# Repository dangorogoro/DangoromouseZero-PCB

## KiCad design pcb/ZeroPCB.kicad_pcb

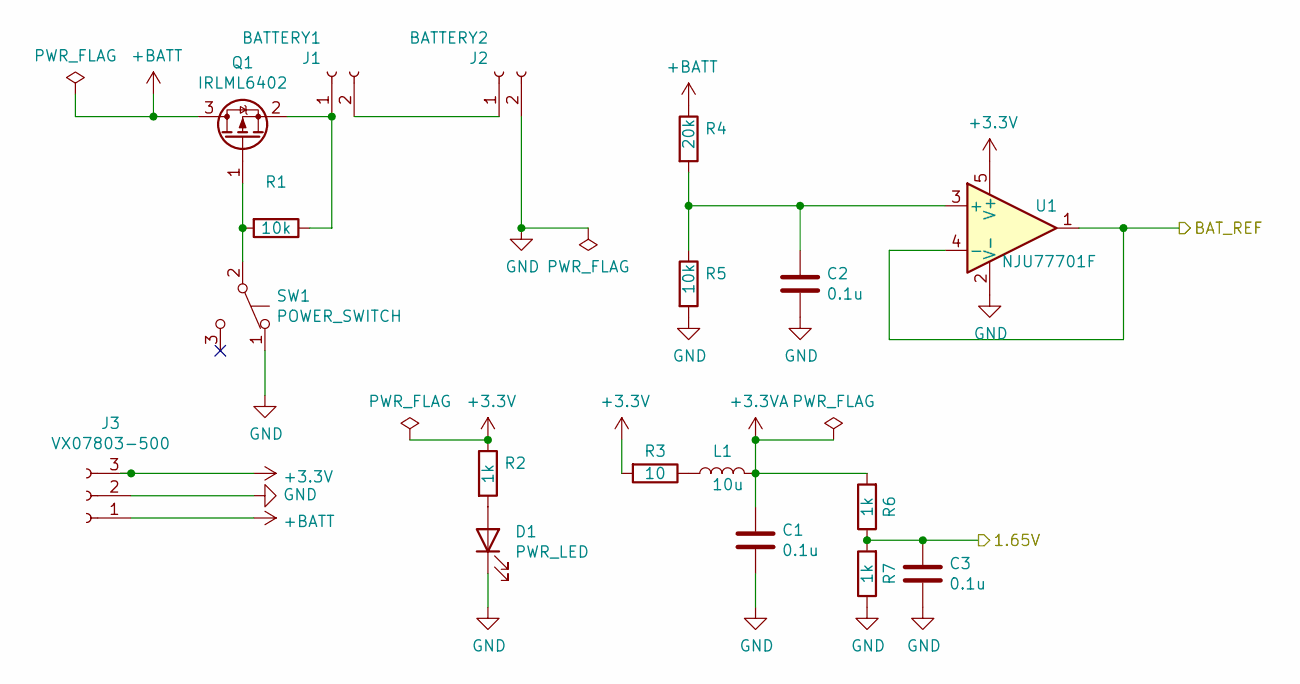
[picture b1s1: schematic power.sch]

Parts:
C1, C2, C3: 0.1u; C_0603_HandSoldering
D1: PWR_LED; LED_0603_HandSoldering
J1: BATTERY1; Molex_PicoBlade_53047-0210_02x1.25mm_Straight
J2: BATTERY2; Molex_PicoBlade_53047-0210_02x1.25mm_Straight
J3: VX07803-500; Pin_Header_Straight_1x03_Pitch2.54mm
L1: 10u; R_1210_HandSoldering
Q1: IRLML6402; SOT-23
R1, R5: 10k; R_0603_HandSoldering
R2, R6, R7: 1k; R_0603_HandSoldering
R3: 10; R_0603_HandSoldering
R4: 20k; R_0603_HandSoldering
SW1: POWER_SWITCH; Pin_Header_Straight_1x03_Pitch2.54mm
U1: NJU77701F; SOT-23-5_HandSoldering

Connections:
+3V3: J3.3, R2.1, R3.2, U1.5 (V+); also elsewhere on the board
+BATT: J3.1, Q1.3 (D), R4.1; also elsewhere on the board
/IRSensor/1.65V: C3.1, R6.1, R7.2; also elsewhere on the board
/MicroController/BAT_REF: U1.1, U1.4 (-); also elsewhere on the board
GND: C1.2, C2.2, C3.2, D1.1 (K), J2.2, J3.2, R5.2, R7.1, SW1.1 (A), U1.2 (V-); also elsewhere on the board
unnamed: C2.1, R4.2, R5.1, U1.3 (+)
unnamed: D1.2 (A), R2.2
unnamed 55: J1.1, Q1.2 (S), R1.1; also elsewhere on the board
unnamed: J1.2, J2.1
unnamed: L1.1, R3.1
unnamed: Q1.1 (G), R1.2, SW1.2 (B)

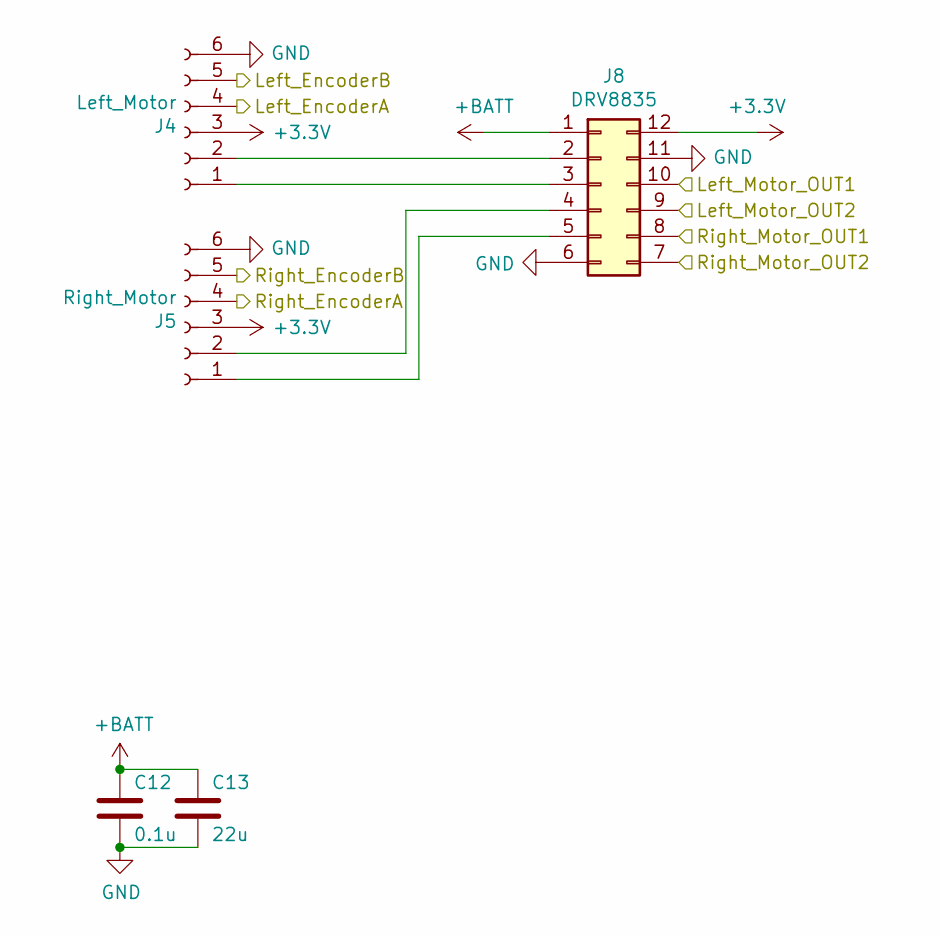
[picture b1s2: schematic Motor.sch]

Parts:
C12: 0.1u; C_0603_HandSoldering
C13: 22u; C_0603_HandSoldering
J4: Left_Motor; JST_XH_B6B-XH-AM_1x06_P2.50mm_Vertical
J5: Right_Motor; JST_XH_B6B-XH-AM_1x06_P2.50mm_Vertical
J8: DRV8835; DRV8835Board

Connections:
+3V3: J4.3, J5.3, J8.12; also elsewhere on the board
+BATT: C12.1, C13.1, J8.1; also elsewhere on the board
/MicroController/Left_EncoderA: J4.4; also elsewhere on the board
/MicroController/Left_EncoderB: J4.5; also elsewhere on the board
/MicroController/Left_Motor_OUT1: J8.10; also elsewhere on the board
/MicroController/Left_Motor_OUT2: J8.9; also elsewhere on the board
/MicroController/Right_EncoderA: J5.4; also elsewhere on the board
/MicroController/Right_EncoderB: J5.5; also elsewhere on the board
/MicroController/Right_Motor_OUT1: J8.8; also elsewhere on the board
/MicroController/Right_Motor_OUT2: J8.7; also elsewhere on the board
GND: C12.2, C13.2, J4.6, J5.6, J8.6, J8.11; also elsewhere on the board
unnamed: J4.1, J8.3
unnamed: J4.2, J8.2
unnamed: J5.1, J8.5
unnamed: J5.2, J8.4

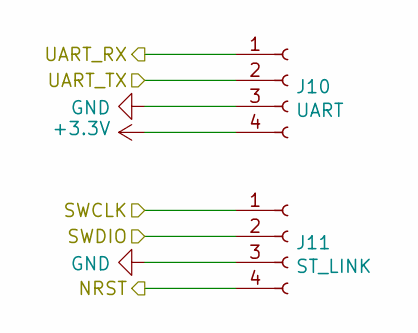
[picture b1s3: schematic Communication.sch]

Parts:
J10: UART; JST_SH_BM04B-SRSS-TB_1x04-1MP_P1.00mm_Vertical
J11: ST_LINK; JST_SH_BM04B-SRSS-TB_1x04-1MP_P1.00mm_Vertical

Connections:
+3V3: J10.4; also elsewhere on the board
/Communication/NRST: J11.4; also elsewhere on the board
/Communication/SWCLK: J11.1; also elsewhere on the board
/Communication/SWDIO: J11.2; also elsewhere on the board
/Communication/UART_RX: J10.1; also elsewhere on the board
/Communication/UART_TX: J10.2; also elsewhere on the board
GND: J10.3, J11.3; also elsewhere on the board

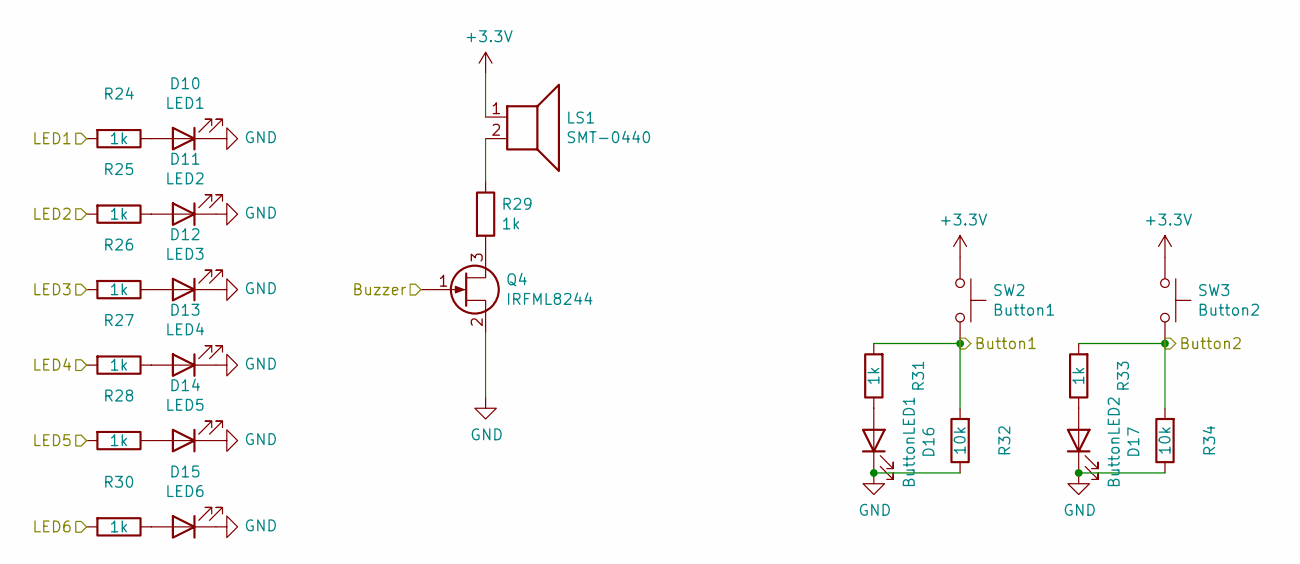
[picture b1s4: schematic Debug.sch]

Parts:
D10: LED1; LED_0603_HandSoldering
D11: LED2; LED_0603_HandSoldering
D12: LED3; LED_0603_HandSoldering
D13: LED4; LED_0603_HandSoldering
D14: LED5; LED_0603_HandSoldering
D15: LED6; LED_0603_HandSoldering
D16: ButtonLED1; LED_0603_HandSoldering
D17: ButtonLED2; LED_0603_HandSoldering
LS1: SMT-0440; SMT-0440-S-R
Q4: IRFML8244; SOT-23
R24, R25, R26, R27, R28, R29, R30, R31, R33: 1k; R_0603_HandSoldering
R32, R34: 10k; R_0603_HandSoldering
SW2: Button1; SW_SPST_EVQP2
SW3: Button2; SW_SPST_EVQP2

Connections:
+3V3: LS1.1, SW2.1, SW3.1; also elsewhere on the board
/Debug/Button1: R31.2, R32.2, SW2.2; also elsewhere on the board
/Debug/Button2: R33.2, R34.2, SW3.2; also elsewhere on the board
/Debug/Buzzer: Q4.1 (G); also elsewhere on the board
/Debug/LED1: R24.2; also elsewhere on the board
/Debug/LED2: R25.2; also elsewhere on the board
/Debug/LED3: R26.2; also elsewhere on the board
/Debug/LED4: R27.2; also elsewhere on the board
/Debug/LED5: R28.2; also elsewhere on the board
/Debug/LED6: R30.2; also elsewhere on the board
GND: D10.1 (K), D11.1 (K), D12.1 (K), D13.1 (K), D14.1 (K), D15.1 (K), D16.1 (K), D17.1 (K), Q4.2 (S), R32.1, R34.1; also elsewhere on the board
unnamed: D10.2 (A), R24.1
unnamed: D11.2 (A), R25.1
unnamed: D12.2 (A), R26.1
unnamed: D13.2 (A), R27.1
unnamed: D14.2 (A), R28.1
unnamed: D15.2 (A), R30.1
unnamed: D16.2 (A), R31.1
unnamed: D17.2 (A), R33.1
unnamed: LS1.2, R29.1
unnamed: Q4.3 (D), R29.2

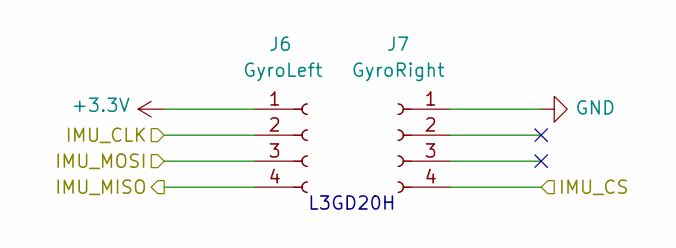
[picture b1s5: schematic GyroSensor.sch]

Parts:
J6: GyroLeft; Pin_Header_Straight_1x04_Pitch2.54mm
J7: GyroRight; Pin_Header_Straight_1x04_Pitch2.54mm

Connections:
+3V3: J6.1, J7.2; also elsewhere on the board
/GyroSensor/IMU_CLK: J6.2; also elsewhere on the board
/GyroSensor/IMU_CS: J6.5; also elsewhere on the board
/GyroSensor/IMU_MISO: J6.4; also elsewhere on the board
/GyroSensor/IMU_MOSI: J6.3; also elsewhere on the board
/IRSensor/IR_Sensor_IN1: J7.3; also elsewhere on the board
/IRSensor/IR_Sensor_IN2: J7.4; also elsewhere on the board
GND: J6.8, J7.1; also elsewhere on the board

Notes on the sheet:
L3GD20H

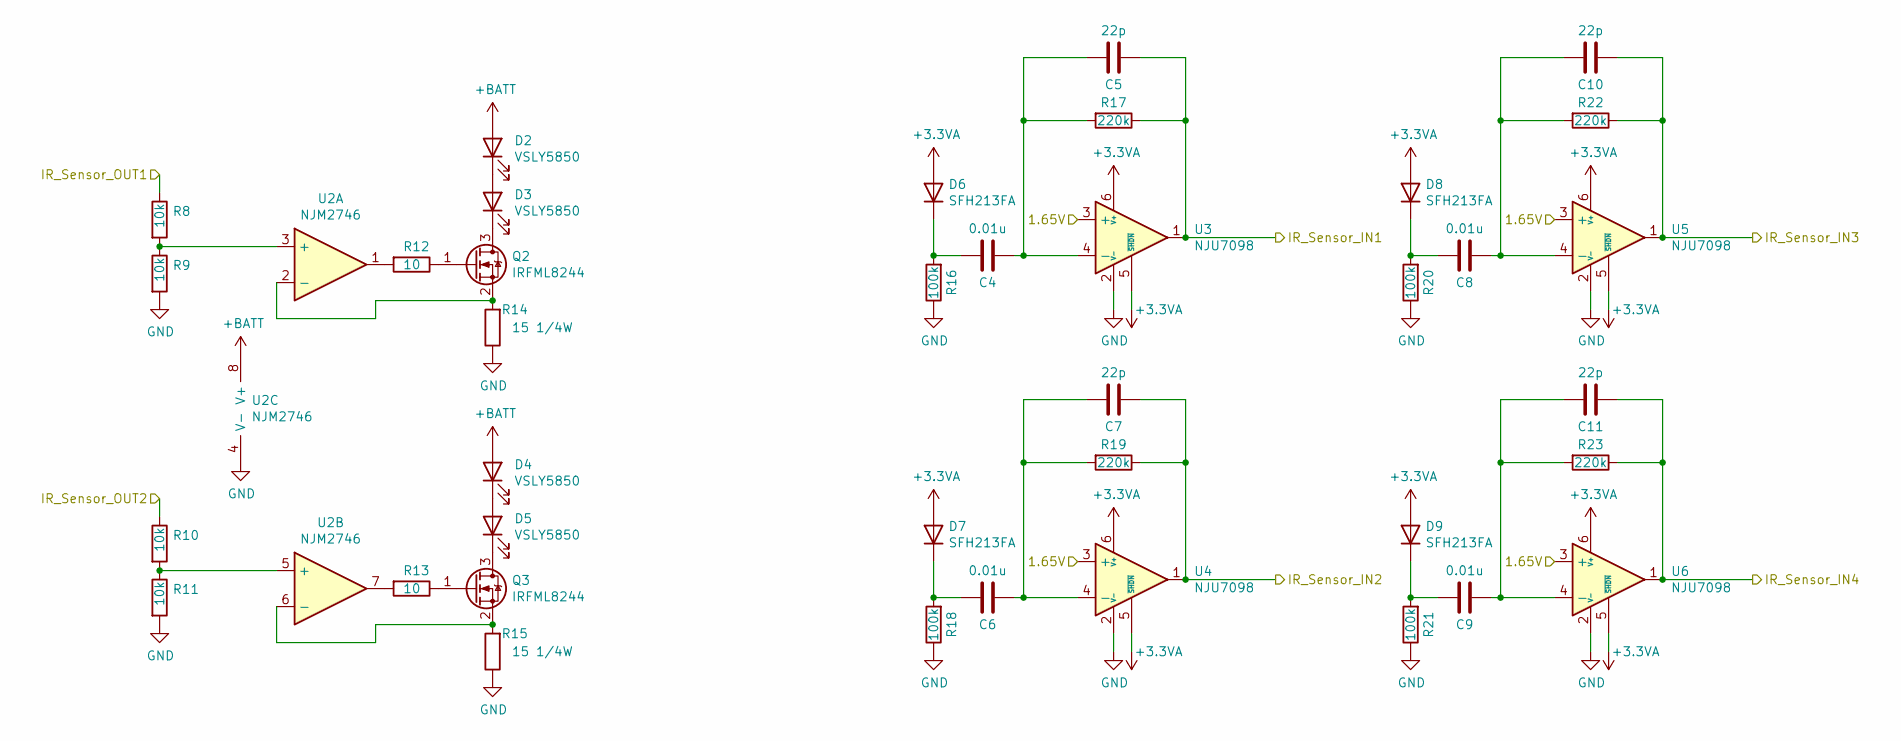
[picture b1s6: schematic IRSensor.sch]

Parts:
C4, C6, C8, C9: 0.01u
C5, C7, C10, C11: 22p
D2, D3, D4, D5: VSLY5850
D6, D7, D8, D9: SFH213FA
Q2, Q3: IRFML8244
R8, R9, R10, R11: 10k
R12, R13: 10
R14, R15: 15 1/4W
R16, R18, R20, R21: 100k
R17, R19, R22, R23: 220k
U2: NJM2746; SOIC-8_3.9x4.9mm_Pitch1.27mm
U3, U4, U5, U6: NJU7098; TSOT-23-6

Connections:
+BATT: D2.2 (A), D4.2 (A), U2.8 (V+); also elsewhere on the board
/IRSensor/1.65V: U3.3 (+), U4.3 (+), U5.3 (+), U6.3 (+); also elsewhere on the board
/IRSensor/IR_Sensor_IN1: C5.1, R17.1, U3.1; also elsewhere on the board
/IRSensor/IR_Sensor_IN2: C7.1, R19.1, U4.1; also elsewhere on the board
/IRSensor/IR_Sensor_IN3: C10.1, R22.1, U5.1; also elsewhere on the board
/IRSensor/IR_Sensor_IN4: C11.1, R23.1, U6.1; also elsewhere on the board
/IRSensor/IR_Sensor_OUT1: R8.1; also elsewhere on the board
/IRSensor/IR_Sensor_OUT2: R10.1; also elsewhere on the board
GND: R9.2, R11.2, R14.1, R15.1, R16.1, R18.1, R20.1, R21.1, U2.4 (V-), U3.2 (V-), U4.2 (V-), U5.2 (V-), U6.2 (V-); also elsewhere on the board
unnamed: C4.1, C5.2, R17.2, U3.4 (-)
unnamed: C6.1, C7.2, R19.2, U4.4 (-)
unnamed: C8.1, C10.2, R22.2, U5.4 (-)
unnamed: C9.1, C11.2, R23.2, U6.4 (-)
unnamed: D2.1 (K), D3.2 (A)
unnamed: D3.1 (K), Q2.3 (D)
unnamed: D4.1 (K), D5.2 (A)
unnamed: D5.1 (K), Q3.3 (D)
unnamed: Q2.1 (G), R12.1
unnamed: Q2.2 (S), R14.2, U2.2 (-)
unnamed: Q3.1 (G), R13.1
unnamed: Q3.2 (S), R15.2, U2.6 (-)
unnamed: R8.2, R9.1, U2.3 (+)
unnamed: R10.2, R11.1, U2.5 (+)
unnamed: R12.2, U2.1
unnamed: R13.2, U2.7

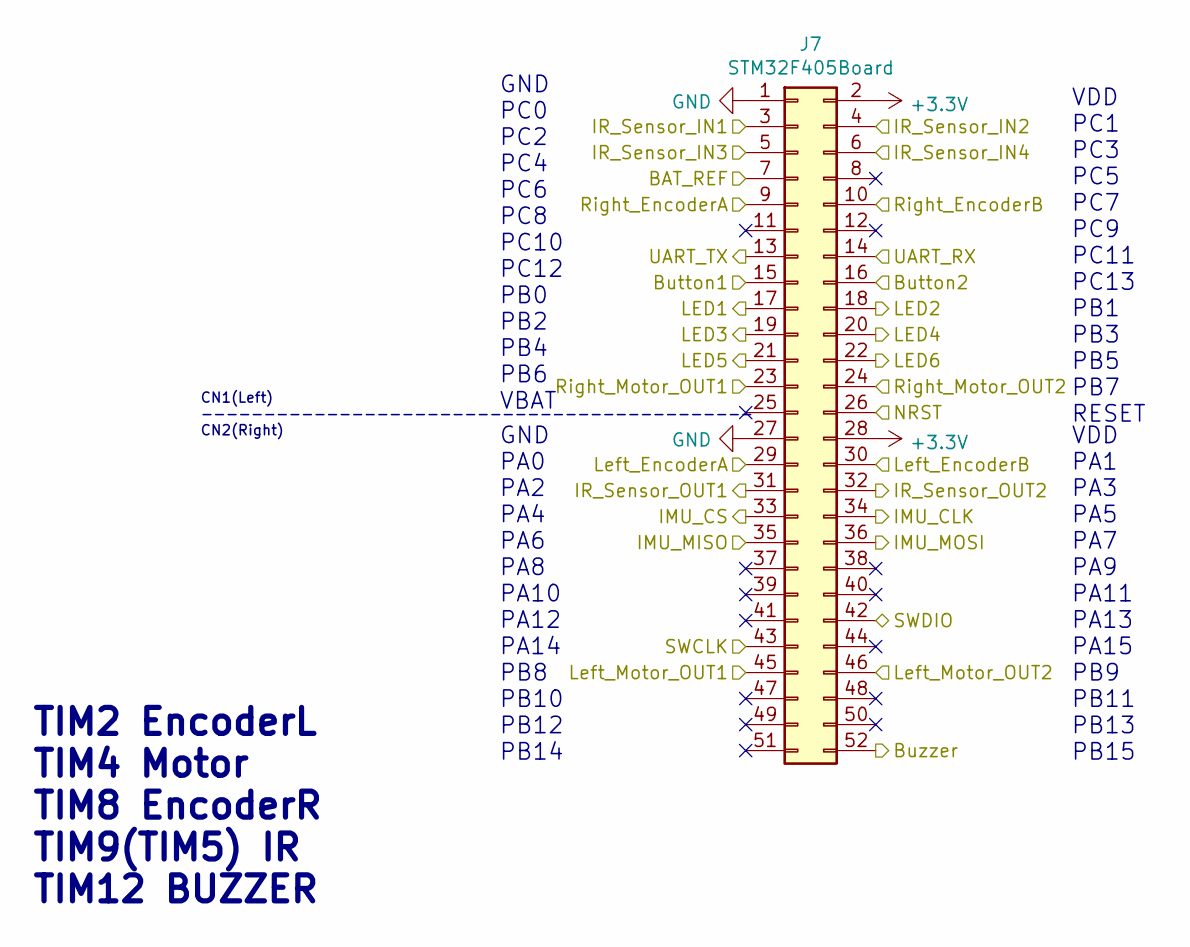
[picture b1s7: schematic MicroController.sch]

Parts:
J7: STM32F405Board

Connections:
+3V3: J7.2, J7.25, J7.28; also elsewhere on the board
/Communication/NRST: J7.26; also elsewhere on the board
/Communication/SWCLK: J7.43; also elsewhere on the board
/Communication/SWDIO: J7.42; also elsewhere on the board
/Communication/UART_RX: J7.14; also elsewhere on the board
/Communication/UART_TX: J7.13; also elsewhere on the board
/Debug/Button1: J7.15; also elsewhere on the board
/Debug/Button2: J7.16; also elsewhere on the board
/Debug/Buzzer: J7.52; also elsewhere on the board
/Debug/LED1: J7.17; also elsewhere on the board
/Debug/LED2: J7.18; also elsewhere on the board
/Debug/LED3: J7.19; also elsewhere on the board
/Debug/LED4: J7.20; also elsewhere on the board
/Debug/LED5: J7.21; also elsewhere on the board
/Debug/LED6: J7.22; also elsewhere on the board
/GyroSensor/IMU_CLK: J7.34; also elsewhere on the board
/GyroSensor/IMU_CS: J7.33; also elsewhere on the board
/GyroSensor/IMU_MISO: J7.35; also elsewhere on the board
/GyroSensor/IMU_MOSI: J7.36; also elsewhere on the board
/IRSensor/IR_Sensor_IN1: J7.3; also elsewhere on the board
/IRSensor/IR_Sensor_IN2: J7.4; also elsewhere on the board
/IRSensor/IR_Sensor_IN3: J7.5; also elsewhere on the board
/IRSensor/IR_Sensor_IN4: J7.6; also elsewhere on the board
/IRSensor/IR_Sensor_OUT1: J7.31; also elsewhere on the board
/IRSensor/IR_Sensor_OUT2: J7.32; also elsewhere on the board
/MicroController/BAT_REF: J7.7; also elsewhere on the board
/MicroController/Left_EncoderA: J7.29; also elsewhere on the board
/MicroController/Left_EncoderB: J7.30; also elsewhere on the board
/MicroController/Left_Motor_OUT1: J7.45; also elsewhere on the board
/MicroController/Left_Motor_OUT2: J7.46; also elsewhere on the board
/MicroController/Right_EncoderA: J7.9; also elsewhere on the board
/MicroController/Right_EncoderB: J7.10; also elsewhere on the board
/MicroController/Right_Motor_OUT1: J7.23; also elsewhere on the board
/MicroController/Right_Motor_OUT2: J7.24; also elsewhere on the board
GND: J7.1, J7.27; also elsewhere on the board

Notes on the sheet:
GND PC0 PC2 PC4 PC6 PC8 PC10 PC12 PB0 PB2 PB4 PB6 VBAT
VDD PC1 PC3 PC5 PC7 PC9 PC11 PC13 PB1 PB3 PB5 PB7 RESET
TIM2 EncoderL TIM4 Motor TIM8 EncoderR TIM9(TIM5) IR TIM12 BUZZER
GND PA0 PA2 PA4 PA6 PA8 PA10 PA12 PA14 PB8 PB10 PB12 PB14
VDD PA1 PA3 PA5 PA7 PA9 PA11 PA13 PA15 PB9 PB11 PB13 PB15
CN1(Left) -------------------------------------------- CN2(Right)

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
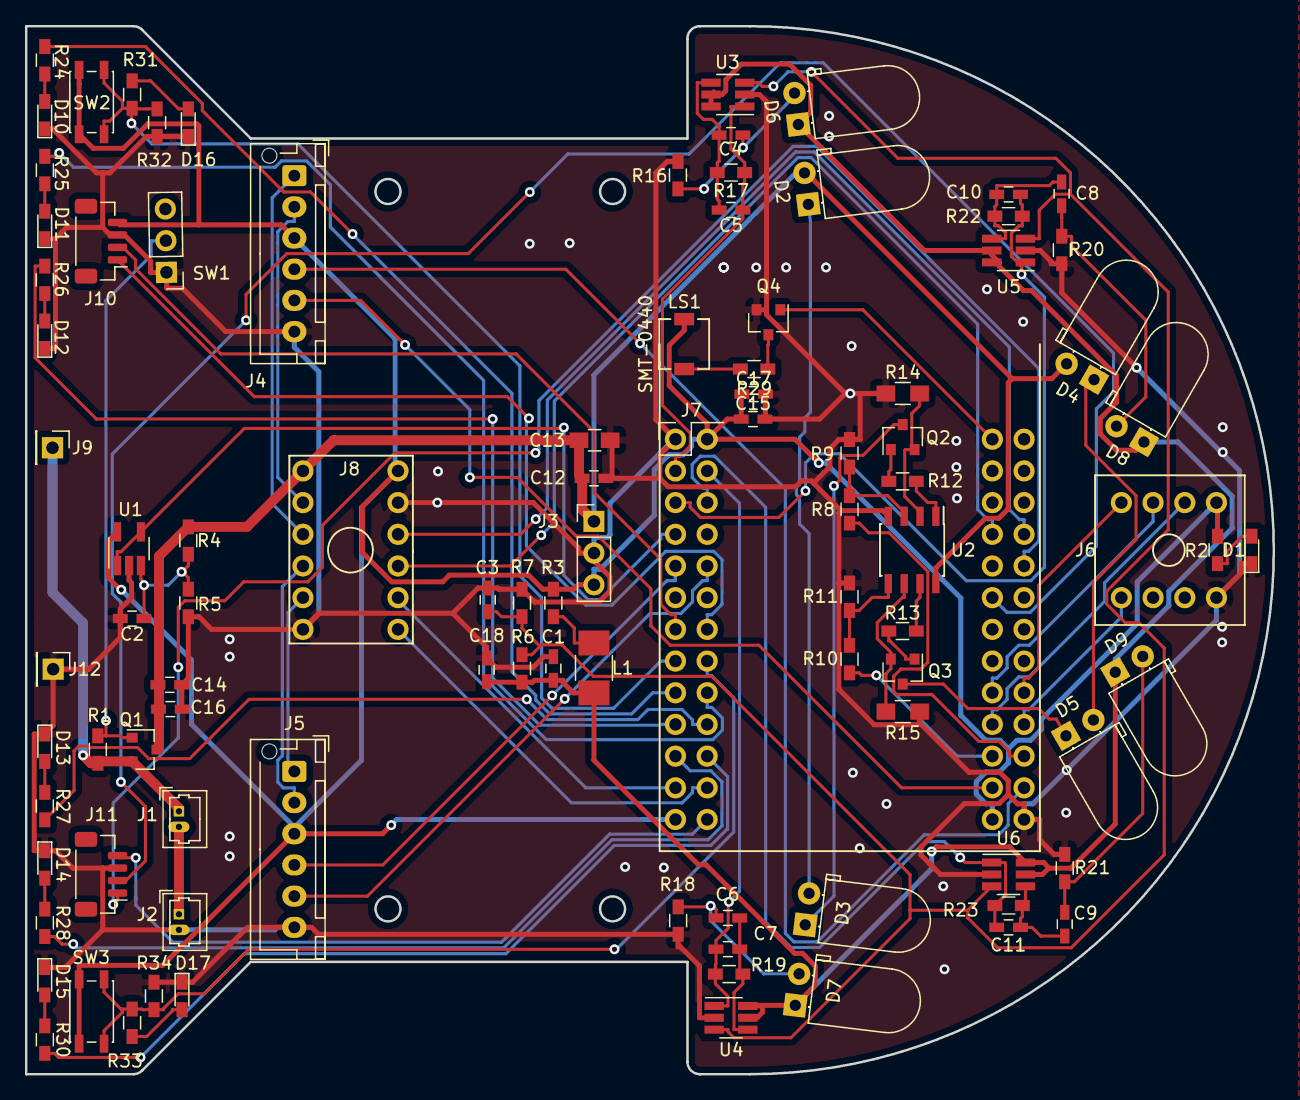
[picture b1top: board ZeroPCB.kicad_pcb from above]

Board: 2 copper layers, 100.0 x 84.0 mm, 96 parts (0 on the bottom side), 78 nets.

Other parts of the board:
C14, C15: 0.1u; C_0603_HandSoldering
C16, C17: 10u; C_0603_HandSoldering
C18: 2.2u; C_0603_HandSoldering
J9: BATT_PIN; Pin_Header_Straight_1x01_Pitch2.54mm
J12: GND_PIN; Pin_Header_Straight_1x01_Pitch2.54mm

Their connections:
+3V3: C15.1, C17.1; also elsewhere on the board
+BATT: C14.1, C16.1; also elsewhere on the board
GND: C14.2, C15.2, C16.2, C17.2, C18.2, J12.1; also elsewhere on the board
unnamed 55: J9.1; also elsewhere on the board

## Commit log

2021-10-11 Finish the schematic
2021-10-13 Add pdf
2021-10-18 Add dxf data
2021-10-18 Add footprint
2021-10-18 Make netlist
2021-10-19 Add footprint for board module
2021-10-19 Update schematic
2021-10-27 Run autorouter
2021-10-27 Update document
2021-10-27 MXのやつ追加
2021-10-31 Change the name of mx project
2021-10-31 Add picture
2021-10-31 Add LTSpice project for ir sensor
2021-10-31 Add a logo footprint
2021-10-31 Make the project for usb charger
2021-10-31 Update pcb
2021-10-31 Add gerder data
2021-11-18 Simulate with NJU77701F
2021-11-18 Export pdf of schematic for usb charger
2021-11-27 Add bom files
2021-11-27 Rename pdf
2021-11-27 Update documents
2021-11-27 Write about where to buy the parts
